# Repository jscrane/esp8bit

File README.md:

View this project on [CADLAB.io](https://cadlab.io/project/24808). 

# esp8bit
8-bit emulator on esp8266

Supports these emulations (with [r65emu](https://github.com/jscrane/r65emu) and [uC-Makefile](https://github.com/jscrane/uC-Makefile)):
- [UK101](https://github.com/jscrane/UK101)
- [PET](https://github.com/jscrane/PET)
- [Apple1](https://github.com/jscrane/Apple1)
- [pacman](https://github.com/jscrane/pacman)
- [invaders](https://github.com/jscrane/invaders)
- [cpm80](https://github.com/jscrane/cpm80)

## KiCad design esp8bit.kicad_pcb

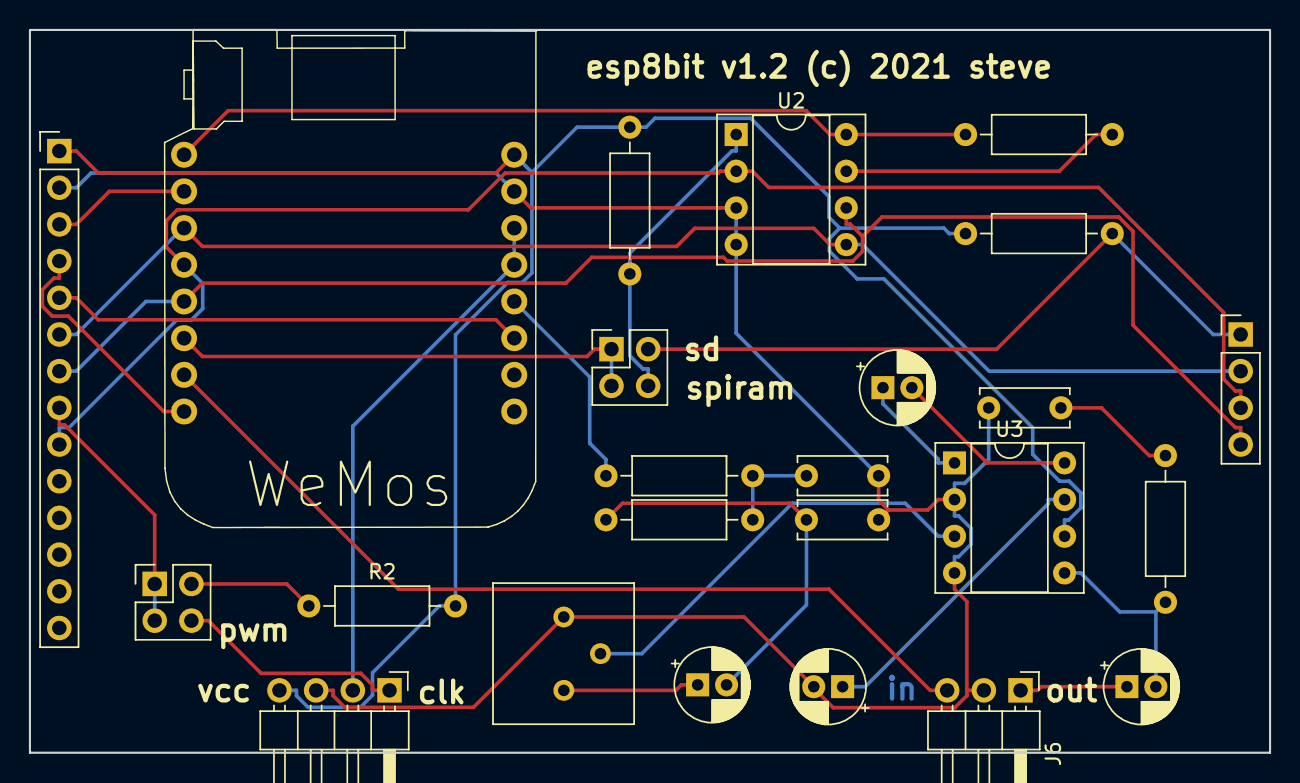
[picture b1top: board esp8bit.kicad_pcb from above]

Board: 2 copper layers, 85.9 x 50.0 mm, 24 parts (0 on the bottom side), 29 nets.

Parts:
C1, C2: 10n; C_Disc_D6.0mm_W2.5mm_P5.00mm
C3, C4, C5: 10u; CP_Radial_D5.0mm_P2.00mm
C6: 100n; C_Disc_D6.0mm_W2.5mm_P5.00mm
C7: 100u; CP_Radial_D5.0mm_P2.00mm
J1: Touchscreen; PinHeader_1x14_P2.54mm_Vertical
J2: SD/RAM; PinHeader_2x02_P2.54mm_Vertical
J3: SD; PinHeader_1x04_P2.54mm_Vertical
J4: KBD; PinHeader_1x04_P2.54mm_Horizontal
J5: Backlight; PinHeader_2x02_P2.54mm_Vertical
J6: Audio; PinHeader_1x03_P2.54mm_Horizontal
R1, R3, R7: 10k; R_Axial_DIN0207_L6.3mm_D2.5mm_P10.16mm_Horizontal
R2: 100R; R_Axial_DIN0207_L6.3mm_D2.5mm_P10.16mm_Horizontal
R4, R5: 27k; R_Axial_DIN0207_L6.3mm_D2.5mm_P10.16mm_Horizontal
R6: 10R; R_Axial_DIN0207_L6.3mm_D2.5mm_P10.16mm_Horizontal
R_POT1: 10k; Potentiometer_Bourns_3386P_Vertical
U1: WeMos_mini; D1_mini_board
U2: 23K256-I_P; DIP-8_W7.62mm_Socket
U3: LM386; DIP-8_W7.62mm_Socket

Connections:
+3V3: R3.1, U1.16, U2.8
/A_IN: J6.3, U1.10
/A_OUT: C7.1, J6.1
/DC: J1.5, U1.6
/KBD_CLK: J4.1, J5.4
/KBD_DATA: J4.2, U1.3, U1.4
/LED: J1.8, J5.1, J5.3
/MISO: J1.9, J3.3, U1.13, U2.2
/MOSI: J1.6, J3.2, U1.14, U2.5
/RAM_CS: J2.4, R1.1, U2.1
/Rst: J1.4, U1.9
/SCK: J1.7, J3.4, U1.12, U2.6
/SD_CS: J2.2, J3.1, R7.1
/SD_RAM_CS: J2.1, J2.3, U1.11
/Sound: R4.2, U1.5
/TFT_CS: J1.3, U1.15
GND: C1.2, C2.2, C5.2, C6.2, J1.2, J4.3, J6.2, R_POT1.3, U1.2, U2.3, U2.4, U3.2, U3.4
unnamed: C1.1, R4.1, R5.2
unnamed: C2.1, C3.2, R5.1
unnamed: C3.1, R_POT1.1
unnamed: C4.1, U3.1
unnamed: C4.2, U3.8
unnamed: C5.1, U3.7
unnamed: C6.1, R6.2
unnamed: C7.2, R6.1, U3.5
unnamed: J5.2, R2.1
unnamed: R3.2, U2.7
unnamed: R_POT1.2, U3.3
VCC: J1.1, J4.4, R1.2, R2.2, R7.2, U1.1, U3.6

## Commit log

2021-10-05 Backlink to CADLAB.io has been added.

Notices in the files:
esp8bit.kicad_pcb:
esp8bit v1.2 (c) 2021 steve
